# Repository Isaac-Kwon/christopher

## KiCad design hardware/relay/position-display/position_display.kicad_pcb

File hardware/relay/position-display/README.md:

# 릴레이식 위치 표시 보드 (모듈 I, 회로도 + 기판 배치)

작성일: 2026-11-16 · 상태: **회로도(KiCad 10) 생성·ERC 0건, 넷리스트 시뮬레이션(26³ 위치 전부, 계수기 공통 보드 넷리스트와 끝에서 끝까지 17,576 클럭)·음성 시험 16/16 통과, 기판 배치(미배선) 생성·DRC 0건, 배선은 사용자가** · 관련: `hardware/relay/layout.md` 3.5·3.8절(모듈 I), `hardware/relay/counter-board/README.md` 5·10절(`POS` 커넥터 J4), `hardware/relay/sequencer/README.md` 11절 5번(`POS` 부하), `docs/decisions/0003-interfaces.md` 2.2절(24 V 레벨), 4.5절(`POS`), 7절(접지·보호), `hardware/common/power-unit.md`(F12, `+24V_L`)

**표기.** **(계산)** = 이 문서의 산술, **(추정)** = 실측 전 값, **(미확인)** = 데이터시트로 확인하지 못한 것.

## 1. 무엇인가

뱅크의 코어 위치 (l, m, r)를 관람객에게 **세 글자**로 보이는 보드다. 입력은 계수기 공통 보드 J4의 `POS`(자리마다 5비트 이진수, 24 V 레벨, 0003 4.5절)이고, 자리마다 **릴레이 접점 나무**가 5비트를 26개 가운데 하나의 램프로 푼다. 램프마다 글자 A–Z가 붙어 있어 켜진 램프가 그 자리의 글자다. 판정에는 관여하지 않는다(0003 4.5절: `POS`는 표시·대조 전용).

| 항목 | 값 |
|---|---|
| 릴레이 | **G6S-2 39개**(자리마다 13개: 비트 0–4에 1, 1, 2, 4, 5개) |
| 글자 램프 | 5 mm LED 78개(자리마다 26) + 직렬 2.7 kΩ |
| 입력 버퍼 | 15채널(`POS` 한 선에 하나): BSS138 + AO3401A + 저항 6 + 커패시터 1, 비트 표시 LED 15 |
| 그 밖 | 역기전력 다이오드 39, 전원 입력 사슬(PTC 0.5 A, 직렬 P채널 MOSFET, TVS, 100 µF), `CHASSIS` 한 벌 |
| 커넥터 | J1 `POS_IN`(D-sub 25 수, 계수기 J4와 같은 핀 배치), J2 `24V_L_IN`(5.08 mm 2극) |
| 부품 합계 | 398개(장착 구멍 4 포함) |
| 기판 | **88 × 294 mm**, 4층. 제어 칸의 오른쪽 띠(폭 90, `layout.md` 3.5절)에 선다 |
| 전원 | `+24V_L`(전원부 F12). 평균 약 0.20 A, 최대 약 0.33 A **(계산, 5절)** |

생성기 `gen_display.py`(회로도), `gen_display_pcb.py`(배치), 검증기 `verify_display.py`(넷리스트), `verify_display_pcb.py`(기판). 공통 도우미 `kigen.py`(심볼은 순서기 보드의 `kilib`, 넷리스트 해석과 계수기 모델은 `counter-board/verify_counter.py`를 그대로 쓴다). UUID를 고정해 두었으므로 생성물을 손으로 고치지 말고 생성기를 고친다.

## 2. 5비트를 글자로: 접점 나무

### 2.1 왜 접점 나무인가

5비트 이진수를 26개 가운데 하나로 푸는 방법은 셋을 보았다.

| 안 | 내용 | 버린 이유 / 고른 이유 |
|---|---|---|
| 화면 | 감시 장치가 `POS`를 읽어 화면에 글자를 띄운다 | 릴레이 기계에서 위치만 전자 화면이 보이게 된다. 화면은 따로 있다(`layout.md` 3.10절) |
| 다이오드 행렬 + 16분할 글자 | 26개 출력에서 다이오드로 획을 고른다(자리마다 약 180개) | 시대에 맞지 않고, 결국 26개로 푸는 단계(접점 나무)가 앞에 또 필요하다 |
| **접점 나무 + 글자마다 램프** | 비트마다 전환 접점을 두 갈래로 나누는 나무. 잎이 26개, 잎마다 램프 하나 | **채택.** 당시의 방식(전화 교환기의 선택 회로, 봄베의 표시 릴레이 + 램프)과 같고, 테스트 레지스터의 정지 표시(글자마다 램프)와 모양이 같다 |

### 2.2 접점의 수를 정직하게 세기

두 갈래 나무에서 잎이 n개면 전환 접점은 n − 1개가 든다. 잎 26개 → **자리마다 전환 접점 25개**(`layout.md` 3.8절의 "25–31개"의 아래 끝) **(계산)**. 나무의 뿌리를 어느 비트에 두느냐에 따라 **비트마다 필요한 극 수**가 달라지고, 한 비트의 극은 같은 코일로 움직이는 릴레이들이 나눠 가진다. G6S-2는 극이 **둘**뿐이다.

| 뿌리 | 비트 0 | 비트 1 | 비트 2 | 비트 3 | 비트 4 | 접점 | G6S-2 (2극) | 4극 릴레이 |
|---|---:|---:|---:|---:|---:|---:|---:|---:|
| 비트 4 (MSB) | 13 | 6 | 3 | 2 | 1 | 25 | 7+3+2+1+1 = **14** | 4+2+1+1+1 = 9 |
| **비트 0 (LSB)** | 1 | 2 | 4 | 8 | 10 | 25 | 1+1+2+4+5 = **13** | 1+1+1+2+3 = 8 |

- LSB 뿌리에서 레벨 b(b < 4)는 아래 b비트의 값 p마다 접점이 하나여서 2^b개다. 레벨 4는 16 + p ≤ 25인 p = 0–9에만 접점이 있고(10개), p = 10–15의 마디는 그대로 램프 10–15다.
- 그래서 **LSB 뿌리, 자리마다 G6S-2 13개, 세 자리 39개**로 정했다. 남는 극은 비트 0 릴레이의 한 극뿐이다.
- 처음 가정(`layout.md` 3.8절, `power-unit.md` 2.1절)의 "종속 릴레이 15개"는 비트마다 릴레이 하나였다. 2극 릴레이로는 나무를 만들 수 없으므로(비트 3에 8극, 비트 4에 10극) 수가 39개로 는다.
- 4극 투명 케이스 범용 릴레이(Omron MY4급)로 하면 자리마다 8개(합 24개)지만 코일이 약 0.9 W(37.5 mA, 0003 7.5절)라 비트 4 하나에 112 mA, 소켓 풋프린트가 KiCad 표준 라이브러리에 없고(PY14·PYF14, **미확인**), 위치마다 비트 0이 1회 동작하는 수명(17,576회/전체 구동)에도 불리하다. 이 보드는 다른 릴레이 보드와 같은 G6S-2로 하고 투명 덮개 너머로 보이게 한다(열린 질문 1).

### 2.3 회로 (자리 d, 글자 D ∈ {L, M, R})

- 넷 `<D>N<b>_<p>` = 레벨 b의 마디(비트 0..b−1의 값이 p). 레벨 0은 보드 `+24V`.
- 비트 b의 접점(마디 p마다 하나): COM = `<D>N<b>_<p>`, NC → 마디 (b+1, p), NO → 마디 (b+1, p + 2^b). 레벨 4: NC → 잎 p, NO → 잎 p + 16.
- 잎 `<D>LAMP<vv>` → 2.7 kΩ → LED `DS<d><vv>`(값 `Lamp X`, X = A + vv) → 0 V.
- 비트 b의 릴레이 `K<d><b><i>`(i = 0..n_b − 1)의 코일은 모두 그 비트의 **코일 버스** `<D>BC<b>`에 병렬이고, 코일마다 역기전력 다이오드(1N4148W).
- 접점 i의 배정: 그 비트의 접점 목록을 p 순서로 두 개씩 끊어 릴레이 i의 극 1(4/3/5), 극 2(9/10/8)에 준다.

**정확히 하나만 켜진다.** 나무의 모든 마디는 닫힌 갈래가 정확히 하나이므로 어떤 릴레이 상태에서도 자리마다 잎 하나만 `+24V`에 닿는다. 그래서 비트 릴레이들이 서로 다른 순간에 넘어가는 전환 중에도 "아무것도 안 켜짐"이나 "둘이 켜짐"이 없다(검증: 무작위 릴레이 상태 3,000개). 전환 중에는 잠시 다른 글자가 켜질 수 있다(표시 전용, 몇 ms).

**계수기가 내지 않는 값 26–31**은 비트 4의 접점이 없는 마디(p = 10–15)로 가서 K–P가 켜진다. 계수기는 0–25만 내므로 문제가 없다. 막으려면 비트 4에 접점 6개(릴레이 3개)가 더 든다(열린 질문 3).

## 3. 입력: `POS` 부하와 버퍼

### 3.1 `POS` 선 하나에 걸리는 것 (계산)

계수기의 `POS` 출력은 슬레이브 릴레이의 접점(+24 V)이고 핀당 30 mA 이하의 부하를 가정했다(`counter-board/README.md` 10절, 0003 2.2절 "내는 쪽 30 mA까지"). 이미 걸린 부하:

| 받는 쪽 | 걸린 선 | 24 V | 26.4 V | 근거 |
|---|---|---:|---:|---|
| 순서기의 추종 릴레이 `KP0/3/4` | `POS10`, `13`, `14` | 12.6 mA | 13.9 mA | 22 kΩ 풀다운 + 6.8 kΩ·LED + 코일 2.88 kΩ(쇼트키 뒤) [`sequencer/seqdesign.py`] |
| 감시 장치(제어 커넥터 7–21번) | 15선 모두 | ≤ 15 mA | ≤ 15 mA | 0003 2.2절 받는 쪽 한도. 단위 시험기는 2.2 kΩ + 광커플러 약 10 mA |

`POS10/13/14`는 이미 **27.6–28.9 mA**를 쓴다. 남는 몫은 1.1 mA다.

- **릴레이로 직접 받으면 넘친다.** 비트 하나에 코일이 최대 5개(비트 4, 41.5 mA), 추종 릴레이 하나(G6S-2, 8.3 mA + 풀다운)만 달아도 26.4 V에서 약 39 mA가 된다.
- 그래서 **버퍼**: 표시 보드의 입력은 전압만 읽는 가벼운 받는 쪽이고, 코일 전류는 표시 보드 자신의 `+24V_L`에서 나온다.

| 선 | 24 V에서 합 | 26.4 V에서 합 | 한도 |
|---|---:|---:|---:|
| `POS10`, `13`, `14` (순서기 + 감시 + 표시) | 28.5 mA | **29.9 mA** | 30 mA |
| 그 밖 12선 (감시 + 표시) | 15.9 mA | 16.0 mA | 30 mA |

(`verify_display.py`가 넷리스트의 저항값으로 다시 계산해 한도를 확인한다.)

### 3.2 입력 채널 (한 선에 하나, 15채널)

```
POS 핀 ─┬─ RP 33k ─ 0 V                        (핀 쪽 풀다운)
        └─ RA 100k ─┬─ BSS138 게이트 ─ RB 18k ∥ CG 100 nF ─ 0 V
                    │  BSS138 소스 = 0 V, 드레인 ─ RC 10k ─┬─ AO3401A 게이트
                    │                         +24V ─ RD 4.7k ─┘
                    └  AO3401A 소스 = +24V, 드레인 = 코일 버스 <D>BC<b> ─ 4.7k ─ 비트 LED
```

| 항목 | 값 (계산) | 요구 |
|---|---|---|
| 게이트 = 핀 전압 × 18/118 | 2.4 V에서 0.37 V, 18 V에서 2.75 V, 26.4 V에서 4.0 V | BSS138 문턱 0.8–1.5 V: 2.4 V 이하에서 꺼짐(≤ 0.6 V), 18 V 이상에서 켜짐(≥ 2.5 V) [0003 2.2절] |
| AO3401A Vgs = −V × 4.7/14.7 | 23.0 V에서 −7.35 V, 26.4 V에서 −8.44 V | Rds(on) 규격 −4.5 V 이하, 절대 최대 ±12 V |
| 받는 쪽 등가 저항 | 33 kΩ ∥ 118 kΩ = 25.8 kΩ, 0.93 mA(24 V), 1.02 mA(26.4 V) | 3.1절의 남는 몫 1.1 mA |
| 게이트 필터 | RB ∥ RA와 100 nF → 약 1.5 ms | 리본 위의 짧은 유도 펄스를 거름. 릴레이 동작(2.5 ms 이상)보다 짧다 |

- 출력은 **+ 쪽 스위칭**(P채널 고측)이다. 코일의 한쪽이 0 V이고 스위치가 + 쪽에 있다는 0003 7.1절의 원칙대로다.
- 비트 LED(맨 위 띠, 자리마다 16 8 4 2 1)는 코일 버스에서 켜진다. 관람객은 이진수와 그것이 푼 글자를 함께 본다.

**0003 2.2절에서 벗어나는 점 두 가지 (의도한 것).**

1. **받는 쪽 등가 저항 ≤ 8 kΩ을 지키지 않는다**(25.8 kΩ). 이 규칙은 누설 0.5 mA의 반도체 출력에서 4 V를 넘지 않게 하려는 것인데, 지키면(≥ 3 mA) 3.1절의 30 mA를 넘는다. 이 보드가 받는 `POS`는 계수기의 **릴레이 접점**이어서 누설이 없다. 누설 0.5 mA인 반도체 출력에 물리면 핀이 12.9 V, 게이트가 2.0 V가 되어 비트가 켜질 수 있다(표시만 틀린다).
2. **`POS10/13/14`의 받는 쪽이 셋**이다(순서기, 감시, 표시). "한 선의 받는 쪽 둘까지"는 전류를 묶으려는 규칙이고 합은 3.1절대로 30 mA 안이다. 이 둘을 0003에 예외로 적을지는 열린 질문 2다.

## 4. 표시면

- **배치(관람객 쪽, 기판 앞면).** 세 자리가 왼쪽부터 l(빠름), m, r(느림)의 세로 줄이다. 줄마다 26개의 램프가 8 mm 피치로 서고 그 왼쪽에 글자 A–Z(실크), 오른쪽에 그 자리의 릴레이 13개(한 릴레이가 램프 두 줄 높이, 비트 순서 0, 1, 2, 2, 3 × 4, 4 × 5)가 있다. 맨 위에 자리 글자와 비트 LED 다섯. 관람객은 켜진 램프 셋에서 위치를 읽고(예: K M Z), 같은 줄의 릴레이가 그 글자를 고르는 것을 본다.
- **앞판.** 제어 칸의 투명 덮개 뒤에 선다. 글자 줄 위에 인쇄한 글자 띠(아크릴, 글자 높이 5 mm, 피치 8)를 대면 실크보다 잘 읽힌다 **(추정)**.
- **램프.** 5 mm 확산형 LED, 2.7 kΩ → 약 7.8 mA(백색 3.0 V 기준), 저항 0.17 W(1206, 정격 0.25 W) **(계산)**. 한 자리에 하나만 켜지므로 램프 전력은 합 23 mA다.
- **계수기가 놓여 있을 때.** 비상 정지·대기(`+24V_SW` 꺼짐, `CK` = `NCK` = 0)에는 `POS`가 모두 0이고 표시는 `A A A`를 보인다. 표시 보드는 `+24V_L`에서 먹으므로 꺼지지 않는다. 이 상태에서는 어차피 `HOME`(= `A A A`)부터 다시 시작한다(`sequencer/README.md` 3.2절).
- **속도.** 빠른 모드(63 ms/위치)에서 l 줄은 초당 약 16번 바뀌어 램프가 흐르는 빛처럼 보이고, 관찰 모드(초당 4 위치 이하)에서는 글자가 하나씩 넘어간다. 표시의 지연은 필터 1.5 ms + 릴레이 2.5–5 ms이고 판정과 무관하다.

## 5. 커넥터와 전원

| 커넥터 | 이름 | 핀 |
|---|---|---|
| J1 (D-sub 25 수) | `POS_IN` | 계수기 공통 J4와 같은 배치: 1–5 l, 6–10 m, 11–15 r(비트 0이 먼저, 24 V = 1), 19–21 0 V, 16–18·22–25 예약(미연결). `POS` 리본(계수기 J4 → 순서기 J5)에 **셋째 압접 소켓**을 달아 꽂는다 |
| J2 (5.08 mm 2극) | `24V_L_IN` | 1 = `+24V_L`(전원부 F12), 2 = 0 V. PTC 0.5 A → 직렬 P채널 MOSFET(드레인 = 공급 쪽, 게이트 제너 12 V + 100 kΩ) → TVS 33 V + 100 µF (0003 7.3절) |
| H1–H4 | 장착 구멍 | M3 도금, `CHASSIS`(J1 껍데기 포함), `CHASSIS`–0 V 1 MΩ ∥ 10 nF (0003 7.1절) |

**전류 (계산, 24 V, 코일 200 mW = 8.3 mA).**

| 부하 | 평균 | 최대 | 근거 |
|---|---:|---:|---|
| 나무 릴레이 | 133 mA (16.1개) | 250 mA (30개) | 값 v에서 켜지는 릴레이 = Σ 비트 × (1, 1, 2, 4, 5). 최대는 v = 25(11001b)의 10개, 세 자리가 모두 25인 마지막 위치 |
| 글자 램프 | 23 mA | 23 mA | 자리마다 하나 |
| 비트 LED + 고측 게이트 분압 | 42 mA | 57 mA | 1인 비트마다 4.7 + 1.6 mA, 평균 6.6비트, 최대 9비트 |
| **합** | **약 0.20 A (4.8 W)** | **약 0.33 A (7.9 W)** | |

`power-unit.md` 2.1절의 "위치 표시 릴레이 15 + 램프 15, 0.86 A"(MY급 릴레이 37.5 mA 가정)는 이 값으로 고쳤다. 보드 PTC는 0.5 A 유지(최대의 1.5배), 전원부 F12(2 A)는 그대로 둔다(보드 PTC보다 크게, 6절 규칙).

## 6. 재생성과 검증

KiCad 10과 Python 3(표준 라이브러리만)이 필요하다. 기판 검증은 KiCad의 `python.exe`(`pcbnew`)를 부른다(`KICAD_PYTHON`, 기본은 `kicad-cli` 옆).

```
python gen_display.py          # 회로도 (position_display.kicad_sch + power, inputs, digit_l/m/r)
python gen_display_pcb.py      # 기판 배치 + 설계 규칙(.kicad_pro)
python verify_display.py       # ERC, 구조, 입력 해석, 26³ 위치, 전환, 계수기와 끝에서 끝까지, 음성 시험 (약 10 s; --quick)
python verify_display_pcb.py   # 기판: 패드 넷, DRC, 래츠네스트, 음성 시험, 결정성 (약 20 s)
```

**넷리스트 검증 `verify_display.py`** (내보낸 넷리스트만 읽는다; 생성기 지식 없음. 릴레이 G6S-2 핀 기능은 계수기 보드와 같은 가정):

- **ERC**(모든 심각도): 위반 **0건**.
- **구조**: 릴레이 39(`POS` 선 1–15마다 코일 버스의 릴레이 수 = 1, 1, 2, 4, 5가 세 번), 코일마다 역기전력 다이오드, 램프 78개의 값이 `Lamp A`–`Lamp Z`이고 참조 번호와 맞음, 전원 입력 사슬(계수기와 같은 검사), 신호 커넥터에 `+24V` 없음, J1의 0 V·예약 핀, `CHASSIS` = H1–H4 + 껍데기 + RCH1/CCH1.
- **입력 해석**: J1 핀마다 넷리스트를 따라 분압 저항 → BSS138 게이트, 드레인 → 저항 → AO3401A 게이트(풀업은 `+24V`), 그 드레인(= 코일 버스)을 찾고, **저항값으로** 게이트 전압·Vgs·등가 저항을 계산해 3.2절의 요구와 3.1절의 부하 한도를 확인한다(15채널 같음).
- **모든 `POS` 값**: (l, m, r) **26³ = 17,576가지** 전부에서 정확히 세 램프 `DS1<l>`, `DS2<m>`, `DS3<r>`만 켜진다(자리마다 26글자 전부). 정보: 26–31은 K–P.
- **전환**: 무작위 릴레이 상태 3,000가지(같은 비트의 릴레이가 따로 놓인 상태 포함)에서 자리마다 램프가 정확히 하나, 단락 없음.
- **끝에서 끝까지**: 계수기 공통 보드의 넷리스트(`counter-board/verify_counter.py`의 스위치 수준 모델)를 `HOME` 뒤 **17,576 클럭** 돌리며 매 클럭 확정·해제 두 시점에서 J4 → 1:1 리본 → 이 보드 J1 → 켜진 글자 = `relay.rs` `Counters`의 (l, m, r). 불일치 0.
- **음성 시험 16종 전부 검출**: 나무 접점 NC/NO 교환 2, J1 핀 교환 2, 램프 F/G 교환, 비트 3 릴레이를 비트 4 버스에, 역기전력 다이오드 반전(단락), 분압 저항값 2(꺼짐·켜짐 문턱), 고측 게이트 저항(Vgs), 고측 MOSFET 소스·드레인 교환, 역방향 전원 MOSFET, 예약 핀에 `+24V`, 장착 구멍을 0 V에, 램프 값의 글자 오류, 핀 쪽 풀다운 제거.
- **결정성**: 다시 만든 회로도 6장이 저장소 파일과 바이트 단위로 같다.

## 7. 기판 배치 (배치만, 배선은 사용자가)

규칙: **PCB = 배치만, 배선 없음**(자동 배선기·외부 다운로드 없음). 외곽, M3 구멍 4개, 모든 풋프린트의 배치, 회로도에서 가져온 넷(래츠네스트), 설계 규칙이 있고 트랙·비아·존은 없다.

| | |
|---|---|
| 파일 | `position_display.kicad_pcb`, `gen_display_pcb.py`(표준 라이브러리만, 계수기 보드와 같은 텍스트 생성 방식) |
| 크기 | **88 × 294 mm**, 4층 |
| 띠 (위에서 아래로) | 자리 글자와 비트 LED(y 9–16) · 입력 버퍼 15칸(자리마다 2 × 3칸, y 18–49) · 글자 줄(램프 26 + 글자 + 저항 + 릴레이 13 + 다이오드, y 52–260) · 전원 사슬·`CHASSIS`(y 263–275) · J1 D-sub 25(아래 변) |
| 풋프린트 / 패드 / 넷 | 398 / 1,081 / 340 |
| 래츠네스트(pcbnew) | **743** = 회로도 넷마다 (패드 수 − 1)의 합 + 같은 번호를 두 번 가진 패드 2(D-sub 껍데기, SOT-223 탭) |
| DRC(`kicad-cli`, 모든 심각도) | **위반 0건**. 회로도 일치: 실제 불일치 0건(심볼 필드 문구, 심볼에 핀이 없는 껍데기 패드 `SH`만 다름) |
| 음성 시험 | 릴레이 패드 두 개의 넷 교환, 풋프린트를 뒷면으로, 껍데기 패드를 0 V로 — 모두 검출 |
| 결정성 | 두 번 만든 `.kicad_pcb`·`.kicad_pro`가 서로, 그리고 저장소 파일과 바이트 단위로 같다 |

넷 클래스: Default 0.2 mm, Rail 0.6 mm(`+24V`, `GND`, `VIN`, `VF`). 코일 버스(≤ 47 mA)와 나무(≤ 8 mA)는 Default로 충분하다. 배선 전에 볼 점: 글자 줄의 릴레이는 90° 돌려 놓았다(코일 핀이 램프 쪽). 나무의 마디는 같은 자리의 릴레이끼리만 이어지므로 줄 안에서 끝난다.

## 8. 열린 질문

1. **보이는 릴레이.** `layout.md`·`concept.md`는 "투명 케이스 종속 릴레이"를 가정했다. 이 보드는 G6S-2(불투명 소형)를 투명 덮개 너머로 보인다. 큰 투명 릴레이를 원하면 2.2절의 4극 안(24개, 코일 버퍼 전류 112 mA/비트, 소켓 풋프린트 작성)으로 바꾼다. 보드 크기는 88 × 294를 넘는다.
2. **0003 2.2절의 두 예외**(3.2절): 받는 쪽 등가 저항 25.8 kΩ, `POS10/13/14`의 받는 쪽 셋. 0003에 "표시 전용 입력" 예외로 적을지, 아니면 순서기의 입력 LED(약 3.2 mA)를 없애 여유를 만들고 이 보드도 ≤ 8 kΩ으로 할지(그러면 26.4 V에서 약 29.6 mA) 결정이 필요하다.
3. **값 26–31을 어둡게 할지.** 계수기는 내지 않는다. 비트 4에 릴레이 3개를 더하면 그때 아무 램프도 켜지지 않게 할 수 있다.
4. **G6S-2 코일 극성·풋프린트**는 다른 릴레이 보드와 같은 가정(핀 1 = +, 핀 12 = −)이다(`shifter-board/README.md` 6절 열린 질문 1).
5. **AO3401A·BSS138**의 문턱과 Vgs 한도는 일반 데이터시트 값으로 잡았다. 구매 품번으로 다시 확인한다 **(미확인)**.

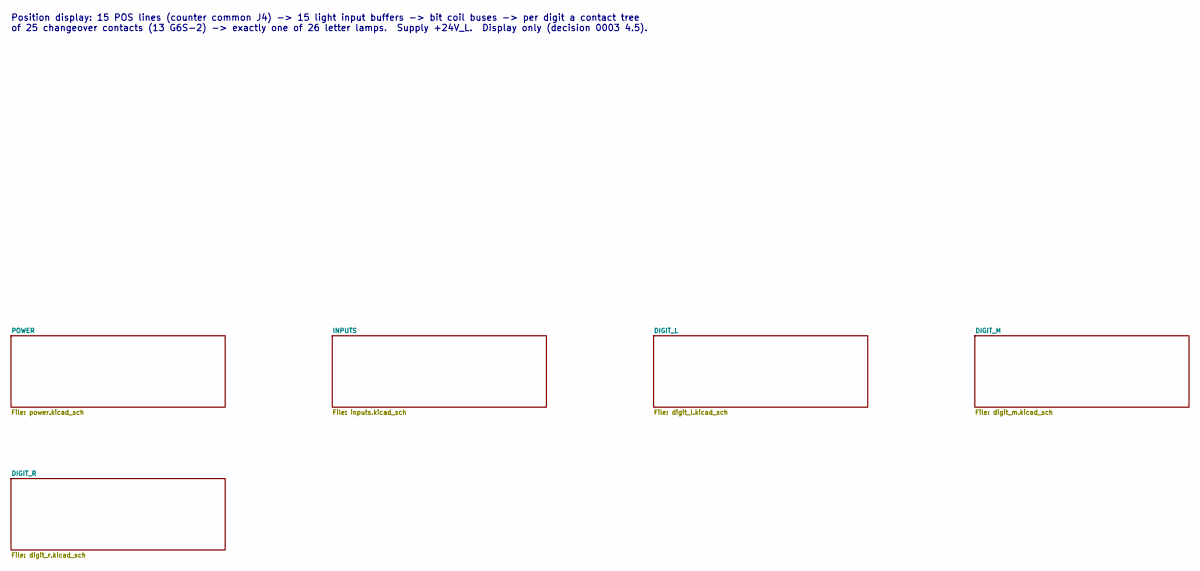
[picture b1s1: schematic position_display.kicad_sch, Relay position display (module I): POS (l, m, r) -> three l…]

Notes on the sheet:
Position display: 15 POS lines (counter common J4) -> 15 light input buffers -> bit coil buses -> per digit a contact tree of 25 changeover contacts (13 G6S-2) -> exactly one of 26 letter lamps. Supply +24V_L. Display only (decision 0003 4.5).

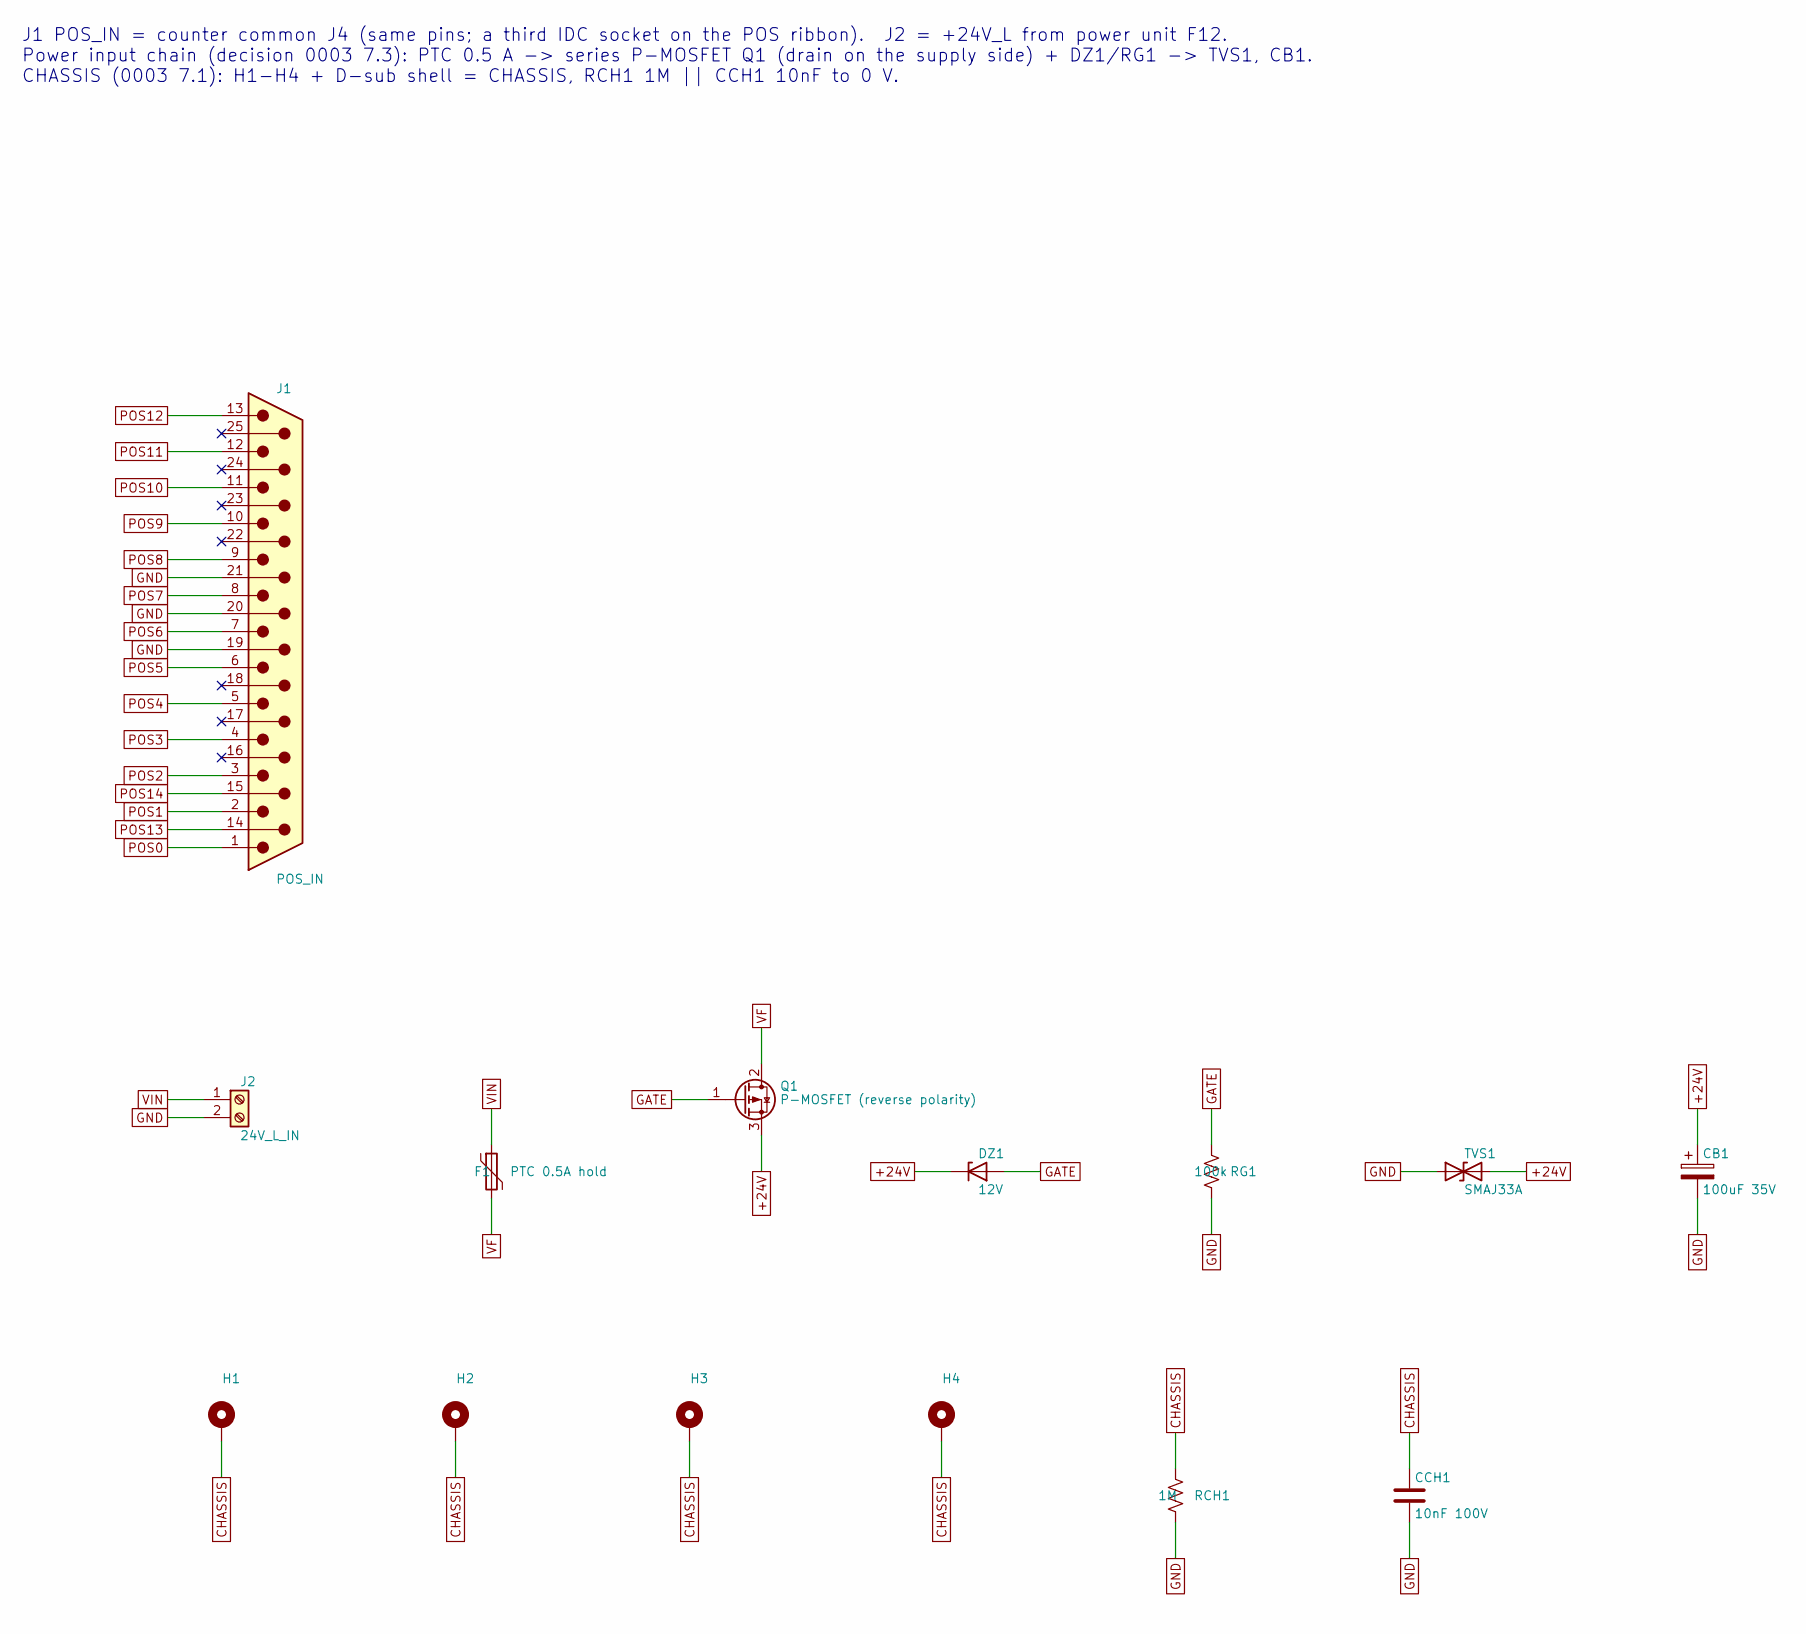
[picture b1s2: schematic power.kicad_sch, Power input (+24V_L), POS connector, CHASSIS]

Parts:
CB1: 100uF 35V; CP_Radial_D8.0mm_P3.50mm
CCH1: 10nF 100V; C_0603_1608Metric
DZ1: 12V; D_SOD-123
F1: PTC 0.5A hold; Fuse_1812_4532Metric
H1, H2, H3, H4: MountingHole_Pad; MountingHole_3.2mm_M3_Pad
J1: POS_IN; DSUB-25_Pins_Horizontal_P2.77x2.84mm_EdgePinOffset9.90mm_Ho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
J2: 24V_L_IN; TerminalBlock_Phoenix_MKDS-1,5-2-5.08_1x02_P5.08mm_Horizont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
Q1: P-MOSFET (reverse polarity); SOT-223-3_TabPin2
RCH1: 1M; R_0603_1608Metric
RG1: 100k; R_0603_1608Metric
TVS1: SMAJ33A; D_SMA

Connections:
+24V: CB1.1, DZ1.1 (K), Q1.3 (S), TVS1.2 (A2); also elsewhere on the board
CHASSIS: CCH1.1, H1.1, H2.1, H3.1, H4.1, J1.SH, RCH1.1
GATE: DZ1.2 (A), Q1.1 (G), RG1.1
GND: CB1.2, CCH1.2, J1.19, J1.20, J1.21, J2.2, RCH1.2, RG1.2, TVS1.1 (A1); also elsewhere on the board
POS0: J1.1; also elsewhere on the board
POS1: J1.2; also elsewhere on the board
POS2: J1.3; also elsewhere on the board
POS3: J1.4; also elsewhere on the board
POS4: J1.5; also elsewhere on the board
POS5: J1.6; also elsewhere on the board
POS6: J1.7; also elsewhere on the board
POS7: J1.8; also elsewhere on the board
POS8: J1.9; also elsewhere on the board
POS9: J1.10; also elsewhere on the board
POS10: J1.11; also elsewhere on the board
POS11: J1.12; also elsewhere on the board
POS12: J1.13; also elsewhere on the board
POS13: J1.14; also elsewhere on the board
POS14: J1.15; also elsewhere on the board
VF: F1.2, Q1.2 (D)
VIN: F1.1, J2.1

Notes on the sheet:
J1 POS_IN = counter common J4 (same pins; a third IDC socket on the POS ribbon). J2 = +24V_L from power unit F12. Power input chain (decision 0003 7.3): PTC 0.5 A -> series P-MOSFET Q1 (drain on the supply side) + DZ1/RG1 -> TVS1, CB1. CHASSIS (0003 7.1): H1-H4 + D-sub shell = CHASSIS, RCH1 1M || C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

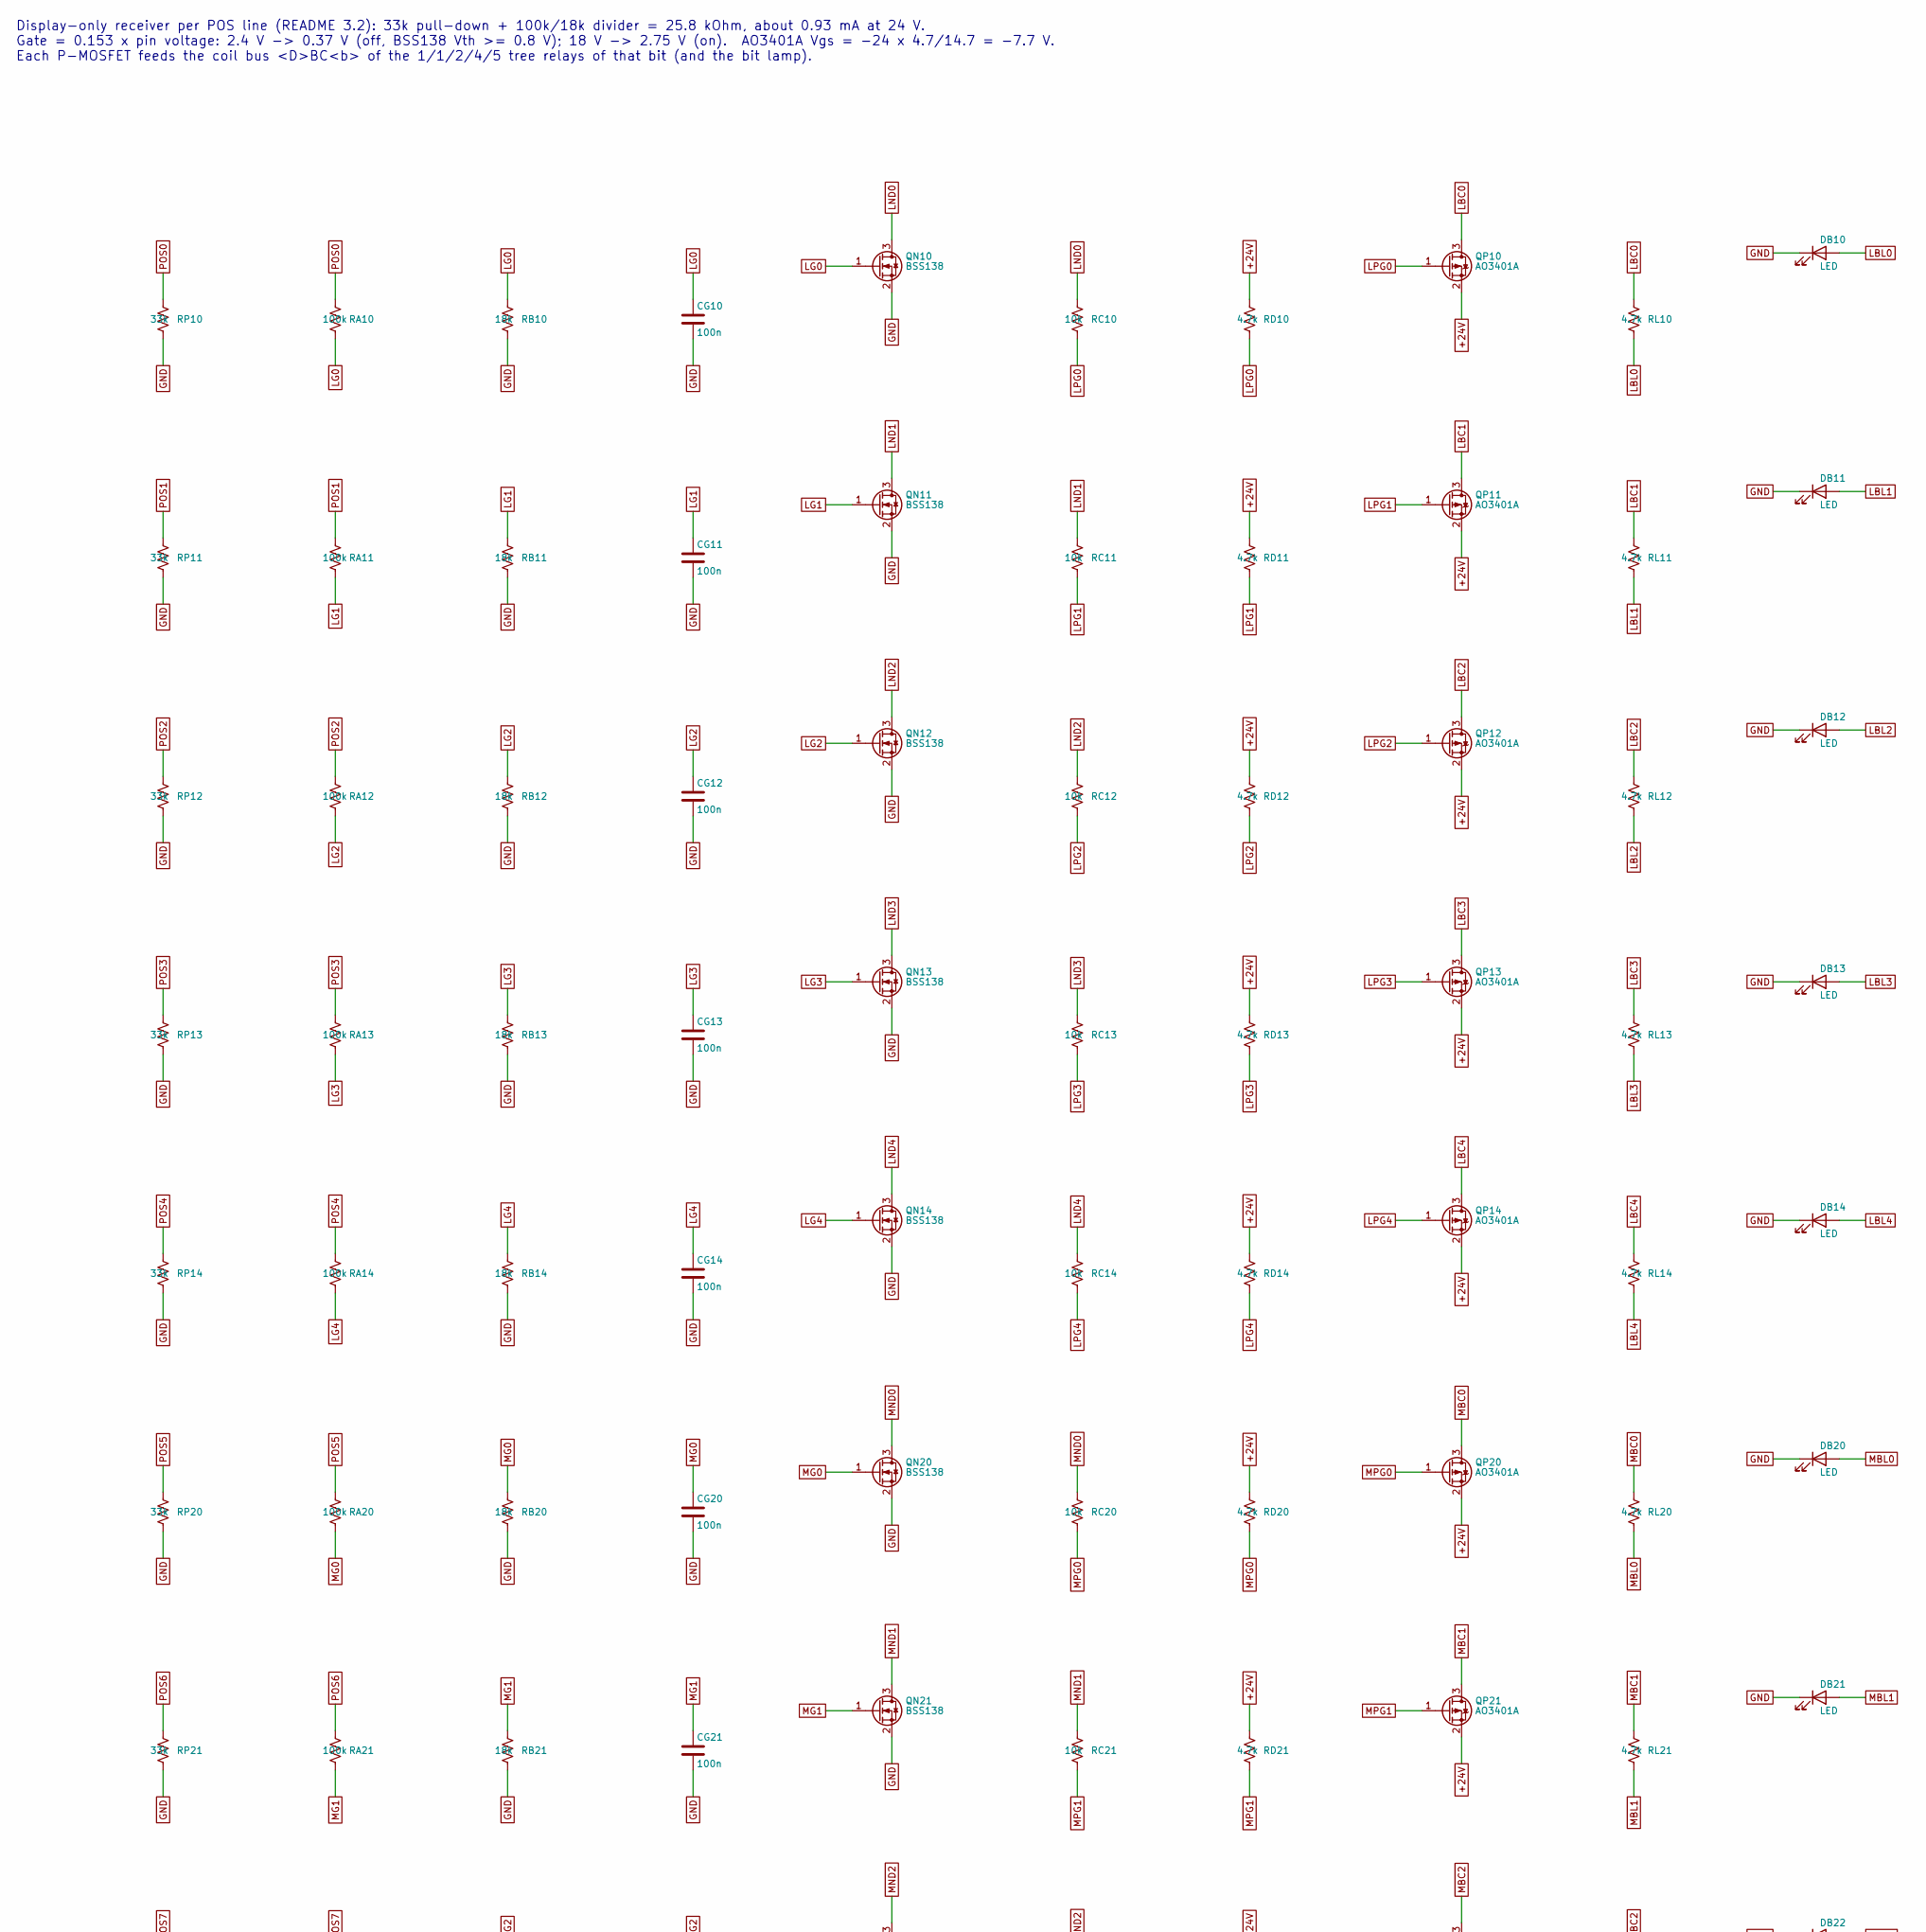
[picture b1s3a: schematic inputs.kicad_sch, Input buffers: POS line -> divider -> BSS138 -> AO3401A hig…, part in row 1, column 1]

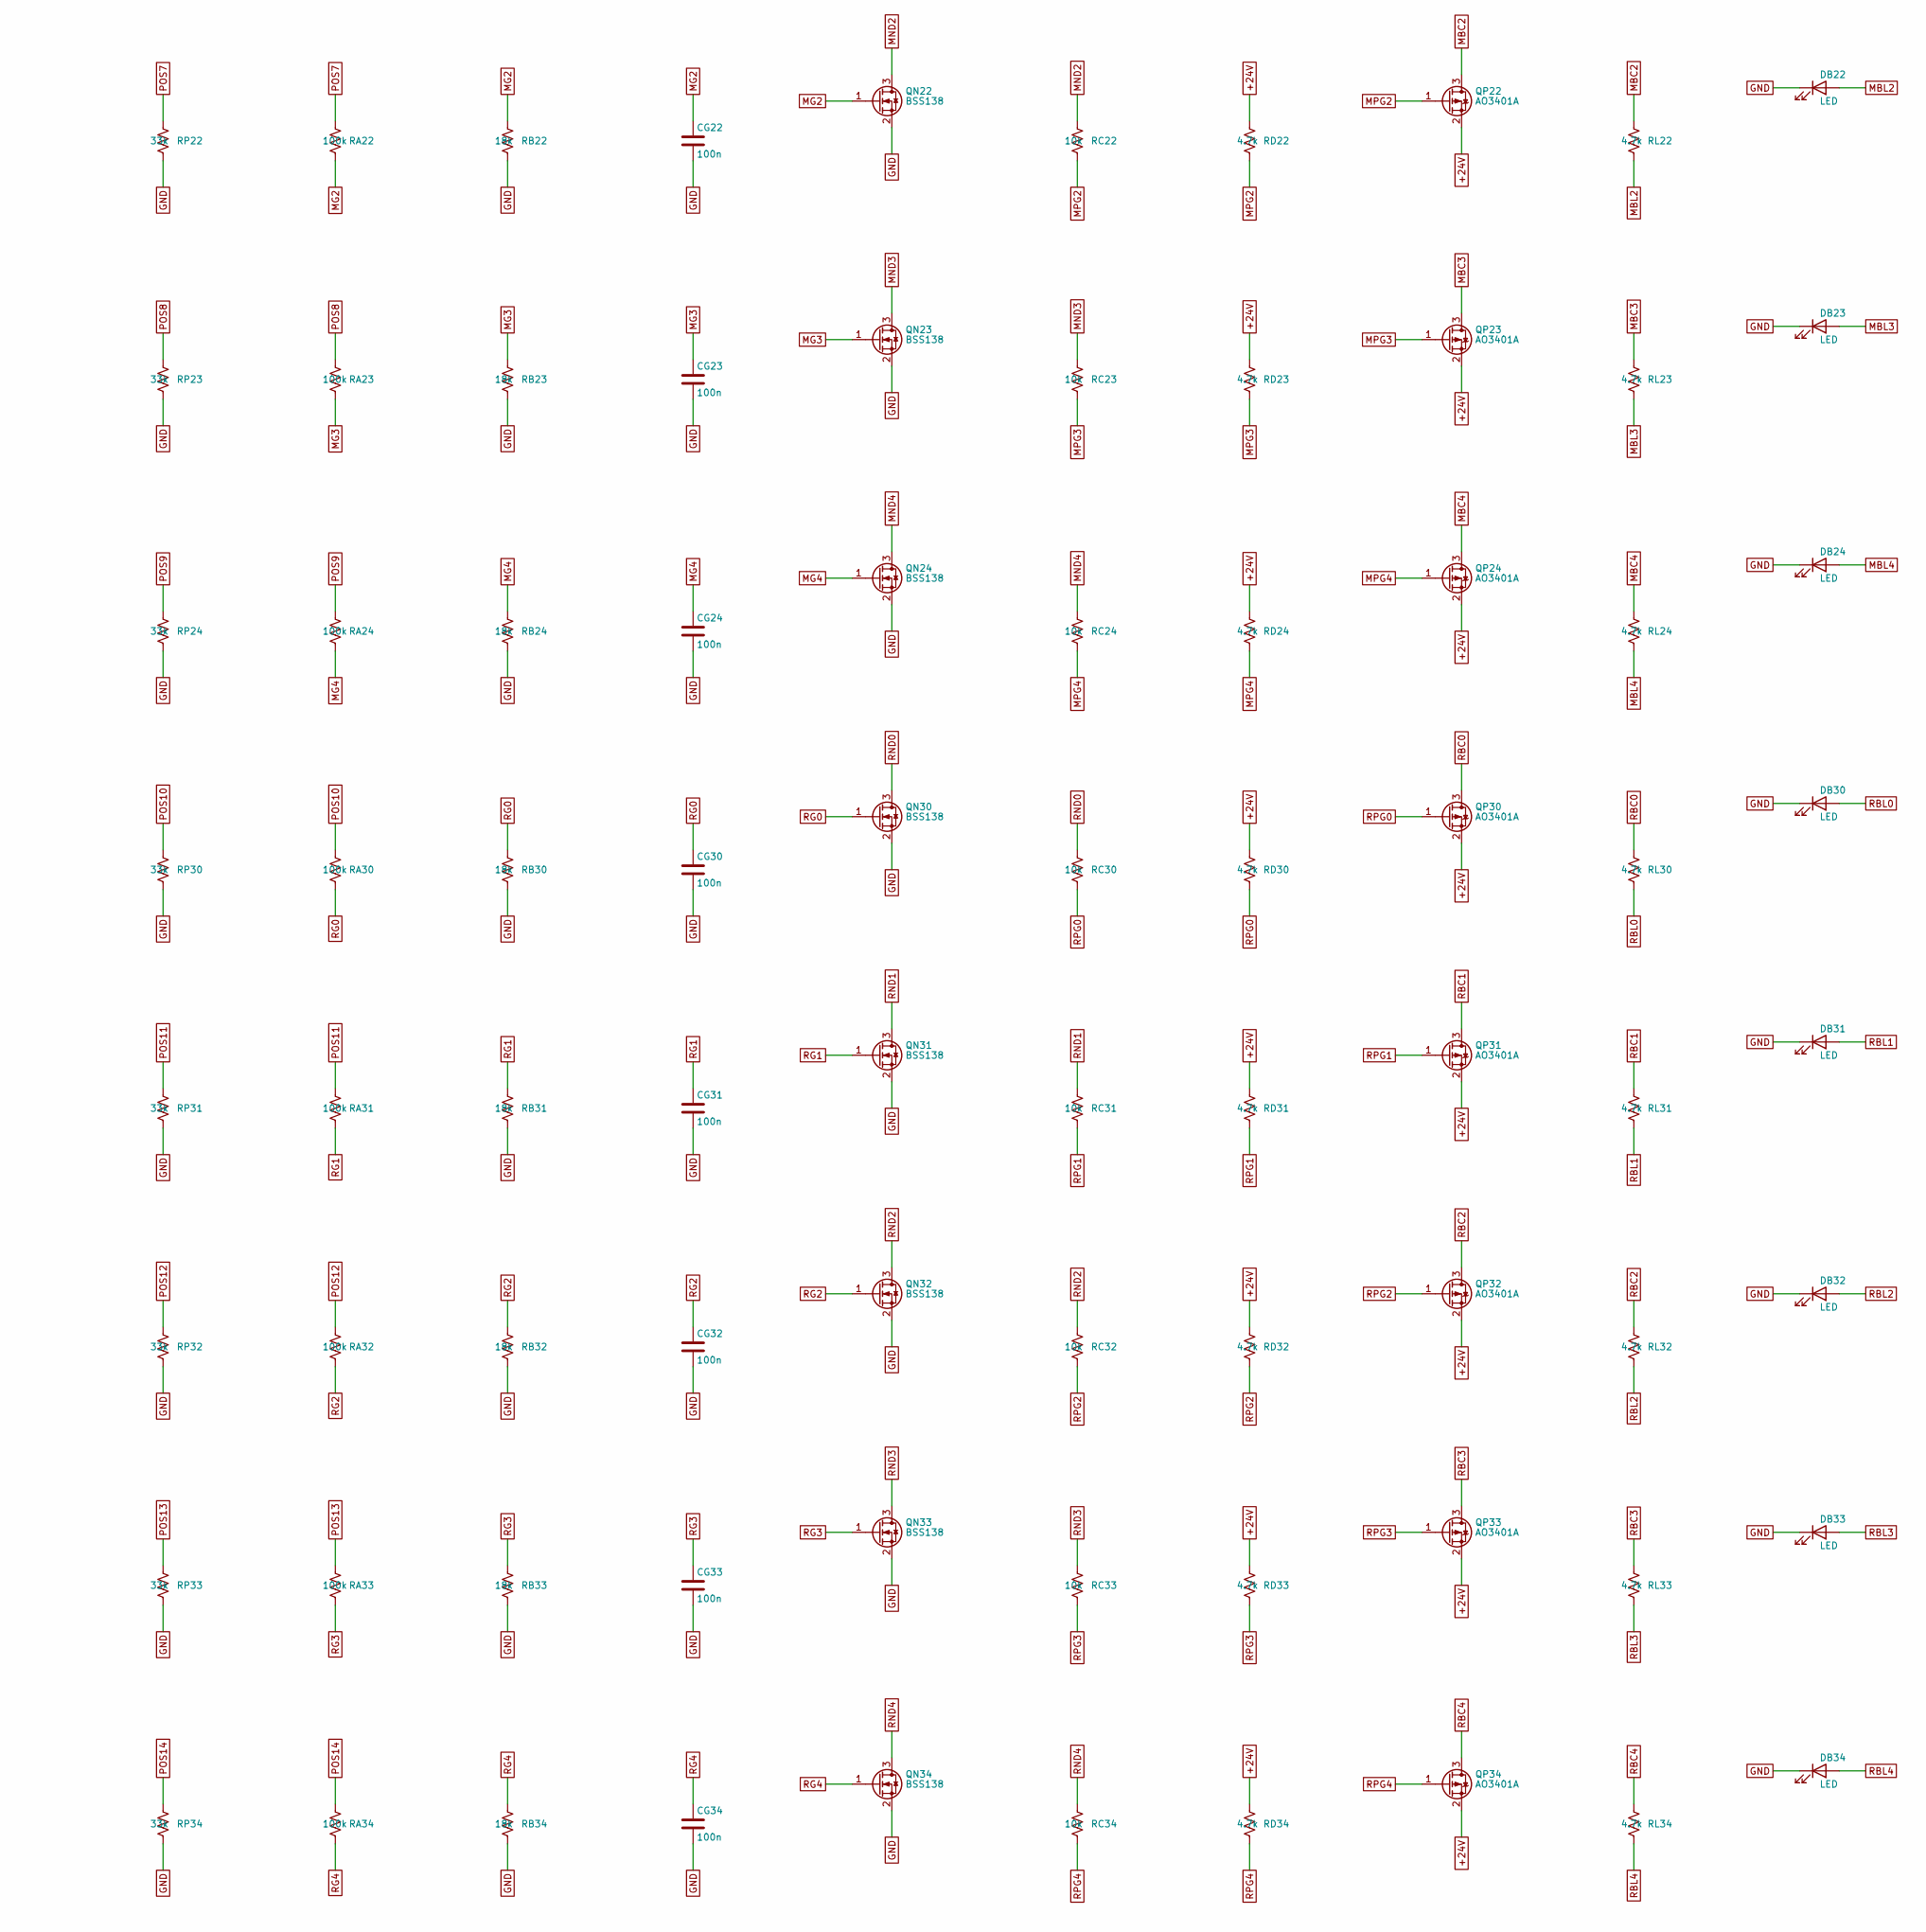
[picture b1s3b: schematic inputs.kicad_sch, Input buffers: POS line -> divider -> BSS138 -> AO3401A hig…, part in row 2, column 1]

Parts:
CG10, CG11, CG12, CG13, CG14, CG20, CG21, CG22, CG23, CG24, CG30, CG31, CG32, CG33, CG34: 100n; C_0603_1608Metric
DB10, DB11, DB12, DB13, DB14, DB20, DB21, DB22, DB23, DB24, DB30, DB31, DB32, DB33, DB34: LED; LED_0603_1608Metric
QN10, QN11, QN12, QN13, QN14, QN20, QN21, QN22, QN23, QN24, QN30, QN31, QN32, QN33, QN34: BSS138; SOT-23
QP10, QP11, QP12, QP13, QP14, QP20, QP21, QP22, QP23, QP24, QP30, QP31, QP32, QP33, QP34: AO3401A; SOT-23
RA10, RA11, RA12, RA13, RA14, RA20, RA21, RA22, RA23, RA24, RA30, RA31, RA32, RA33, RA34: 100k; R_0603_1608Metric
RB10, RB11, RB12, RB13, RB14, RB20, RB21, RB22, RB23, RB24, RB30, RB31, RB32, RB33, RB34: 18k; R_0603_1608Metric
RC10, RC11, RC12, RC13, RC14, RC20, RC21, RC22, RC23, RC24, RC30, RC31, RC32, RC33, RC34: 10k; R_0603_1608Metric
RD10, RD11, RD12, RD13, RD14, RD20, RD21, RD22, RD23, RD24, RD30, RD31, RD32, RD33, RD34: 4.7k; R_0603_1608Metric
RL10, RL11, RL12, RL13, RL14, RL20, RL21, RL22, RL23, RL24, RL30, RL31, RL32, RL33, RL34: 4.7k; R_0603_1608Metric
RP10, RP11, RP12, RP13, RP14, RP20, RP21, RP22, RP23, RP24, RP30, RP31, RP32, RP33, RP34: 33k; R_0603_1608Metric

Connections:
+24V: QP10.2 (S), QP11.2 (S), QP12.2 (S), QP13.2 (S), QP14.2 (S), QP20.2 (S), QP21.2 (S), QP22.2 (S), QP23.2 (S), QP24.2 (S), QP30.2 (S), QP31.2 (S), QP32.2 (S), QP33.2 (S), QP34.2 (S), RD10.1, RD11.1, RD12.1, RD13.1, RD14.1, RD20.1, RD21.1, RD22.1, RD23.1, RD24.1, RD30.1, RD31.1, RD32.1, RD33.1, RD34.1; also elsewhere on the board
GND: CG10.2, CG11.2, CG12.2, CG13.2, CG14.2, CG20.2, CG21.2, CG22.2, CG23.2, CG24.2, CG30.2, CG31.2, CG32.2, CG33.2, CG34.2, DB10.1 (K), DB11.1 (K), DB12.1 (K), DB13.1 (K), DB14.1 (K), DB20.1 (K), DB21.1 (K), DB22.1 (K), DB23.1 (K), DB24.1 (K), DB30.1 (K), DB31.1 (K), DB32.1 (K), DB33.1 (K), DB34.1 (K), QN10.2 (S), QN11.2 (S), QN12.2 (S), QN13.2 (S), QN14.2 (S), QN20.2 (S), QN21.2 (S), QN22.2 (S), QN23.2 (S), QN24.2 (S), QN30.2 (S), QN31.2 (S), QN32.2 (S), QN33.2 (S), QN34.2 (S), RB10.2, RB11.2, RB12.2, RB13.2, RB14.2, RB20.2, RB21.2, RB22.2, RB23.2, RB24.2, RB30.2, RB31.2, RB32.2, RB33.2, RB34.2, RP10.2, RP11.2, RP12.2, RP13.2, RP14.2, RP20.2, RP21.2, RP22.2, RP23.2, RP24.2, RP30.2, RP31.2, RP32.2, RP33.2, RP34.2; also elsewhere on the board
LBC0: QP10.3 (D), RL10.1; also elsewhere on the board
LBC1: QP11.3 (D), RL11.1; also elsewhere on the board
LBC2: QP12.3 (D), RL12.1; also elsewhere on the board
LBC3: QP13.3 (D), RL13.1; also elsewhere on the board
LBC4: QP14.3 (D), RL14.1; also elsewhere on the board
LBL0: DB10.2 (A), RL10.2
LBL1: DB11.2 (A), RL11.2
LBL2: DB12.2 (A), RL12.2
LBL3: DB13.2 (A), RL13.2
LBL4: DB14.2 (A), RL14.2
LG0: CG10.1, QN10.1 (G), RA10.2, RB10.1
LG1: CG11.1, QN11.1 (G), RA11.2, RB11.1
LG2: CG12.1, QN12.1 (G), RA12.2, RB12.1
LG3: CG13.1, QN13.1 (G), RA13.2, RB13.1
LG4: CG14.1, QN14.1 (G), RA14.2, RB14.1
LND0: QN10.3 (D), RC10.1
LND1: QN11.3 (D), RC11.1
LND2: QN12.3 (D), RC12.1
LND3: QN13.3 (D), RC13.1
LND4: QN14.3 (D), RC14.1
LPG0: QP10.1 (G), RC10.2, RD10.2
LPG1: QP11.1 (G), RC11.2, RD11.2
LPG2: QP12.1 (G), RC12.2, RD12.2
LPG3: QP13.1 (G), RC13.2, RD13.2
LPG4: QP14.1 (G), RC14.2, RD14.2
MBC0: QP20.3 (D), RL20.1; also elsewhere on the board
MBC1: QP21.3 (D), RL21.1; also elsewhere on the board
MBC2: QP22.3 (D), RL22.1; also elsewhere on the board
MBC3: QP23.3 (D), RL23.1; also elsewhere on the board
MBC4: QP24.3 (D), RL24.1; also elsewhere on the board
MBL0: DB20.2 (A), RL20.2
MBL1: DB21.2 (A), RL21.2
MBL2: DB22.2 (A), RL22.2
MBL3: DB23.2 (A), RL23.2
MBL4: DB24.2 (A), RL24.2
MG0: CG20.1, QN20.1 (G), RA20.2, RB20.1
MG1: CG21.1, QN21.1 (G), RA21.2, RB21.1
MG2: CG22.1, QN22.1 (G), RA22.2, RB22.1
MG3: CG23.1, QN23.1 (G), RA23.2, RB23.1
MG4: CG24.1, QN24.1 (G), RA24.2, RB24.1
MND0: QN20.3 (D), RC20.1
MND1: QN21.3 (D), RC21.1
MND2: QN22.3 (D), RC22.1
MND3: QN23.3 (D), RC23.1
MND4: QN24.3 (D), RC24.1
MPG0: QP20.1 (G), RC20.2, RD20.2
MPG1: QP21.1 (G), RC21.2, RD21.2
MPG2: QP22.1 (G), RC22.2, RD22.2
MPG3: QP23.1 (G), RC23.2, RD23.2
MPG4: QP24.1 (G), RC24.2, RD24.2
POS0: RA10.1, RP10.1; also elsewhere on the board
POS1: RA11.1, RP11.1; also elsewhere on the board
POS2: RA12.1, RP12.1; also elsewhere on the board
POS3: RA13.1, RP13.1; also elsewhere on the board
POS4: RA14.1, RP14.1; also elsewhere on the board
POS5: RA20.1, RP20.1; also elsewhere on the board
POS6: RA21.1, RP21.1; also elsewhere on the board
POS7: RA22.1, RP22.1; also elsewhere on the board
POS8: RA23.1, RP23.1; also elsewhere on the board
POS9: RA24.1, RP24.1; also elsewhere on the board
POS10: RA30.1, RP30.1; also elsewhere on the board
POS11: RA31.1, RP31.1; also elsewhere on the board
POS12: RA32.1, RP32.1; also elsewhere on the board
POS13: RA33.1, RP33.1; also elsewhere on the board
POS14: RA34.1, RP34.1; also elsewhere on the board
RBC0: QP30.3 (D), RL30.1; also elsewhere on the board
RBC1: QP31.3 (D), RL31.1; also elsewhere on the board
RBC2: QP32.3 (D), RL32.1; also elsewhere on the board
RBC3: QP33.3 (D), RL33.1; also elsewhere on the board
RBC4: QP34.3 (D), RL34.1; also elsewhere on the board
RBL0: DB30.2 (A), RL30.2
RBL1: DB31.2 (A), RL31.2
RBL2: DB32.2 (A), RL32.2
RBL3: DB33.2 (A), RL33.2
RBL4: DB34.2 (A), RL34.2
RG0: CG30.1, QN30.1 (G), RA30.2, RB30.1
RG1: CG31.1, QN31.1 (G), RA31.2, RB31.1
RG2: CG32.1, QN32.1 (G), RA32.2, RB32.1
RG3: CG33.1, QN33.1 (G), RA33.2, RB33.1
RG4: CG34.1, QN34.1 (G), RA34.2, RB34.1
RND0: QN30.3 (D), RC30.1
RND1: QN31.3 (D), RC31.1
RND2: QN32.3 (D), RC32.1
RND3: QN33.3 (D), RC33.1
RND4: QN34.3 (D), RC34.1
RPG0: QP30.1 (G), RC30.2, RD30.2
RPG1: QP31.1 (G), RC31.2, RD31.2
RPG2: QP32.1 (G), RC32.2, RD32.2
RPG3: QP33.1 (G), RC33.2, RD33.2
RPG4: QP34.1 (G), RC34.2, RD34.2

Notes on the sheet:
Display-only receiver per POS line (README 3.2): 33k pull-down + 100k/18k divider = 25.8 kOhm, about 0.93 mA at 24 V. Gate = 0.153 x pin voltage: 2.4 V -> 0.37 V (off, BSS138 Vth >= 0.8 V); 18 V -> 2.75 V (on). AO3401A Vgs = -24 x 4.7/14.7 = -7.7 V. Each P-MOSFET feeds the coil bus <D>BC<b> of the 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
